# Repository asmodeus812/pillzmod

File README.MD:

# Pillz Mod for the Kinesis Advantage/Contoured

This project replaces my two previous forks ([kinesismod](https://github.com/dcpedit/kinesismod) and [kint](https://github.com/dcpedit/kint)) for adding Blackpill support to the Kinesis keyboard.  I've decided to merge all the features into a single PCB, add optional thumb cluster PCBs as part of the kit, and renamed the project to avoid confusion.  Below is a list of supported features.

* Supports Blackpill development board running QMK/Vial
* Supports Pill Bug wireless Bluetooth development board running ZMK
* Optional reversible thumb cluster PCB for left/right sides.  (Maintains original matrix wiring)
* 2u stabilizer support on thumb cluster

## "Pro" PCB Features

* Supports devlopment board with Pro-Micro footprint (Elite-C, Elite-Pi, Nice!Nano)
* Header for connecting up to 3 foot-pedals
* Piezo audio buzzer
* Header for extra data pin (Elite-C only)

## Split PCB (physically split Advantage 2)

_Seen from underneath (component side): right half on the left._

Two narrow boards in [`pcb-split/`](pcb-split/README.md), one per half, for
cutting the case in the middle. Each half has its own Nice!Nano, battery
socket, power switch and reset button, and connects to the same Molex and
Pillz thumb connectors at their original positions. Gerbers are in
`pcb-split/production`.

## Attribution

Credit goes to the following people for doing all the initial development on replacment PCBs for the Kinesis:
 * Aaron Silman's [kinesismod project](https://gitlab.com/Silman/kinesismod.git) ([blog](https://silman.io/project/kinesis_mod/))
 * Michael Stapelberg's [KinT project](https://github.com/kinx-project/kint) ([blog](https://michael.stapelberg.ch/posts/2020-07-09-kint-kinesis-keyboard-controller/))
 * Dmitry Nosachev's [Kin80 project](https://github.com/DmNosachev/kin80)

## Ordering PCBs from JLCPCB

The files needed for https://jlcpcb.com are located in the production folders:
* Choose `pcb-pro/production`, `pcb/production` or `pcb-split/production/left` + `right`
* `thumb-pcb/production`

Once uploaded, you place the order with the selected default options.  You can optionally change the solder mask color, which changes the final color of your PCB.

## Main PCB build guide
### Components
| Position | Description | Qty | Notes |
| -------- | ----------- | --- | ----- |
| J1-J4    | Molex 39-53-2135 | 2 - 6  | [Link](https://octopart.com/39-53-2135-molex-7670149?r=sp)
| J3-J4    | Molex 39-53-2134 | 0 - 2  | Contoured only, [Link](https://octopart.com/search?q=Molex+39-53-2134)
| U1       | Header pins (1x20) | 2 | Should come with dev board
| U1       | Headers (1x20) | 2 | To socket your dev board
| D1-D4    | 1.8mm LED | 4 | [Amazon](https://a.co/d/90uynIs)
| R1-R4    | 10k resistor | 4 | Affects LED brightness. Smaller = brighter |
|          | USB-C panel mount | 1 | [AliExpress](https://www.aliexpress.us/item/3256806463941289.html?spm=a2g0o.order_list.order_list_main.43.18a31802pDYB6d&gatewayAdapt=glo2usa), [Amazon](https://a.co/d/cRoqHqx)

### Blackpill Components
| Position | Description | Qty | Notes |
| -------- | ----------- | --- | ----- |
| U1       | Blackpill (STM32F411) | 1 | [WeAct Store](https://www.aliexpress.com/store/1101545918?spm=a2g0o.order_list.order_list_main.2.18a31802pDYB6d)

#### -or- Pill Bug for wireless build

| Description | Qty | Notes |
| ----------- | --- | ----- |
| Pill Bug | 1 | [MechWild Store](https://mechwild.com/product/pillbug/)
| 3.7V battery | 1 | [2000mAh](https://a.co/d/dVUdHxi)
| Power button | 1 | Optional, [10mm](https://a.co/d/i33uBM0) or [19mm](https://a.co/d/fYN6ZX5)

### Additional "Pro" Components

| Position | Description | Qty | Notes |
| -------- | ----------- | --- | ----- |
| U1       | Elite-C/Elite-Pi | 1 |
|          | 3.7V battery | 1 | [2000mAh](https://a.co/d/dVUdHxi)
| U2       | 74HC595      | 1 | [Amazon](https://a.co/d/eLX9kOY)
| U2       | 16-pin IC socket | 1 | [Amazon](https://a.co/d/5EaFAHo)
| D6-D8    | 1n4148 Diode | 3 | [Link](https://www.mouser.com/ProductDetail/512-1N4148TR)
| BZ1      | Piezo Buzzer | 1 | [Link](https://www.digikey.com/en/products/detail/tdk-corporation/PS1240P02BT/935924)
| SW1      | Reset button | 1 | [Link](https://www2.mouser.com/ProductDetail/Alps-Alpine/SKQGAEE010?qs=N5Jky1br14PyTRvcw7F3eQ%3D%3D)
| R5-R19   | 10k Resistor | 15| AVR/Elite-C Only [Link](https://www.mouser.com/ProductDetail/YAGEO/MFR-12FTF52-10K?qs=oAGoVhmvjhzLlUYKKBtdYQ%3D%3D), [Link](https://mou.sr/3xgqcNf)

#### -or- Nice!Nano for wireless build

| Description | Qty | Notes |
| ----------- | --- | ----- |
| Nice!Nano    | 1 | [Website](https://nicekeyboards.com/nice-nano/)
| 3.7V battery | 1 | [2000mAh](https://a.co/d/dVUdHxi)
| Power button | 1 | Optional, [10mm](https://a.co/d/i33uBM0) or [19mm](https://a.co/d/fYN6ZX5)

### Instructions

_NOTE: If you're using a battery that's larger than 500mAh, then bridge the charge boost jumper labeled JP1 with some solder.  This will increases the max charge rate from 100mA to 500mA. Doing this for small batteries (<500mAh) may cause explosions._

All components go on the side with the silkscreen labels (rectangles) EXCEPT for the LEDs.  First solder the header pins onto your development board, and the header sockets onto the PCB.  I prefer to use Mill-Max 310 series sockets because the pins are thin.  Then solder in the LED resistors, but NOT the actual LEDs yet.  The resistors can be SMD or through hole.

For a wireless build, you can now solder the battery wires/connector to the board.  Make sure the positive wire goes into "BAT+", and the negative wire goes into "BAT-".  If you're using a power button, make sure to wire it inline along the BAT+ wire so that it essentially opens and closes the circuit.

Insert your development board into the sockets on the PCB.

For the Molex connectors, I find that it's more convient to desolder the ones on the original PCB so that I don't have to purchase new ones.  Solder the connectors onto the PCB.

Flip the PCB over and insert the LEDs on the side of the PCB with no other components.  Make sure the short leg goes into the square pad, and bend the legs so that they stay in place.  Screw the PCB back into the keyboard case, making sure the LEDs are lined up with the existing case holes.  You can also adjust the height of the LED to move them closer to the status window if you'd like.  Once you're satisfied with the position of the LEDs, you can then solder them in place while the PCB is still mounted.

Lastly, plug the USB-C panel mount cable to into the development board, and secure the other end to the hole in the case.

### "Pro" Additional Instructions

The components required for this build and their position will depend on the development board you're using.  For example, pull-down resistors R5-R19 are only needed for AVR chips (Pro-Micro, Elite-C) since they don't support internal pull-downs for the row inputs.  Use the image below as a guide.

The Elite-C has an extra B0 pin that is broken out into the J10 pins.  You can use this to drive other components if you choose (ie. RGB strip, Solenoid)

* Pin 1 (square pad) - VCC
* Pin 2 - B0
* Pin 3 - GND

The J9 pins are for foot pedals and have the following assignment:

* Pin 1 (square pad) - Col6
* Pin 2 - Row0
* Pin 3 - Row1
* Pin 4 - Row2

Diodes D6-D8 are connected to the rows, so no additional diodes are needed in the pedals/switches.

### "Pro" Nice!Nano Additional Instructions

Mill-Max 310 sockets are recommended for socketing the Nice!Nano because thin pins are required for connecting the extra 3 pins in the middle.

The Nice!Nano is one pin short of supporting all 4 status lights on the Advantage.  If you want to utilize the unused numpad status LED as a power indicator, go ahead and short JP1 with some solder.

## Thumb cluster PCB build guide

The wiring for the thumb cluster (a.k.a. matrix wiring) has not been altered from original, so theoretically, they can be used in conjunction with any Kinesis PCB, including the stock one.

The PCB is also reversible, so you don't have to place separate orders for a "left" version and a "right" version.

### Components

| Description | Qty | Notes |
| ----------- | --- | ----- |
| 1N4148 SOD-123 diode | 12 | [Amazon](https://a.co/d/gsv8bGT)
| MX switch | 12 | Can desolder and reuse
| 2u screw-in stabilizer | 4 | [Link](https://divinikey.com/products/durock-v2-stabilizers-screw-in)
| Cable connector (1x10) | 4 | 2.54mm pitch (eg KF2510)
| Ribbon cable | 2 | >= 50mm length

### Instructions

You will need two PCBs for the thumb cluster, but since they're reversible, you will need to read the silkscreen to see if it's the left or right cluster.

First step is to solder all the 1N4148 diodes.  Orientation matters, so make sure the line on the diode faces same direction as the thicker white line on the PCB.  Place a dab of solder on ONE of the two diode pads.  Drop the diode into position (double checking the orientation), hold the diode in place with tweezers, and melt the solder you just added to the pad so that diode is held in place.  Now add solder to the opposite pad, thus holding the other diode leg in place.  Repeat for all the other diodes.

The connector for the ribbon cable can now be soldered onto the PCB, and will be on the same side as the diodes.  The pin pitch is 2.54mm, so any compatible connector/cable will work here.

Install the 2u stabilizers onto the PCB.

Now solder in your MX switches.  If you're reusing the original switches, desolder them from the original PCB, and remove the diode from inside the switch housing.  Using a switch opener will make this task much easier.

Mount the thumb clusters onto the keyboard and connect the ribbon cables.

## QMK firmware for "Pro"

* `firmware/pro_qmk_avr_default.bin`
* `firmware/pro_qmk_rp2040_default.uf2`

QMK source: https://github.com/dcpedit/qmk_firmware/tree/pillzmod/keyboards/dcpedit/pillzmod

## Vial firmware for Blackpill

* `firmware/blackpill_vial.bin`
* `firmware/dcpedit_kint_bp_vial_6layers.bin`

Source: https://github.com/dcpedit/vial-qmk/tree/pillzmod/keyboards/dcpedit/pillzmod

Remap keys: https://vial.rocks/

### Flashing firmware under Linux
The file firmware/dcpedit_kint_bp_vial_6layers.bin (or other) can simply be flashed to the Blackpill using the dfu-util. The dfu-util tool requires root privileges if settings are not accessible by the user.

Connect Blackpill to your Linux PC via USB C cable and start unit in DFU mode by holding bootp button and pressing reset button. Wait a second and release the bootp button.

Check the DFU devices by running
```
dfu-util -l
```
The Blackpill device should be visible.

Write the firmware to the device with
```
dfu-util -d 0483:df11 -a 0 -s 0x08000000 -D [PATH TO kint]/firmware/dcpedit_kint_bp_vial_6layers.bin
```

## Vial firmware for "Pro"

* `firmware/pro_vial_avr.hex`

Source: https://github.com/dcpedit/vial-qmk/tree/pillzmod/keyboards/dcpedit/pillzmod
(You will need to clone the entire branch since I had to make a core code change in `spi_master.c`)

## ZMK firmware for Pill Bug

* `firmware/zmk_default.uf2` - Default keymap
* `firmware/zmk_custom.uf2` - Support for up to 6 layers
* `firmware/zmk_reset.uf2` - Resets PillBug board for BT connectivity issue on MacOS      
* `firmware/zmk_studio.uf2` - Studio compatible (Progrm + Esc to unlock)

Source: https://github.com/dcpedit/zmk/tree/pillzmod/app/boards/shields/pillzmod

### Bluetooth with ZMK

The ZMK firmware has mappings for performing system tasks. By default there are 4 Bluetooth pairings saved to the keyboard but they do not switch automatically when adding new devices. So after you add the first device, you need to tell they keyboard to use Bluetooth slot 2 and so forth.
The keys to switch between are accessed by a different keyboard layer. This layer is opened by holding down the "Program" key at the very top right of the Kinesis and, while holding it, then clicking another key as follows:

* **Clear all saved Bluetooth profiles:** Program + F9
* **Bluetooth profile 1:** Program + F1
* **Bluetooth profile 2:** Program + F2
* **Bluetooth profile 3:** Program + F3
* **Bluetooth profile 4:** Program + F4
* **Enter bootloader mode (to upload UF2 files):** Program + - (the dash key just below program)

If you want to do a ZMK firmware build using GitHub actions, take a look at the following repository from keepitsimplejim:

https://github.com/keepitsimplejim/zmk-config-pillzmod-kinesis-adv

## ZMK firmware for "Pro" Nice!Nano

* `firmware/pro_zmk.uf2` - Default keymap
* `firmware/pro_zmk_studio.uf2` - Studio compatible (Progrm + Esc to unlock)

Source: https://github.com/dcpedit/zmk/tree/pillzmod/app/boards/shields/pillzmod_pro
Studio: https://zmk.studio/

## KiCad

All the PCBs were designed using KiCad, which is free and can be downloaded here: https://www.kicad.org/

For the thumb cluster PCB, I wasn't able to figure out how to have the left and right wiring co-exist without errors while sharing the same connector footprint.  My workaround was to first change the connector's reference designator to "J1", update the PCB from schematic, and wire up the left side.  Then I changed the reference designator to "J2", updated the PCB from schematic again, and wired up the right side.

If there are any KiCad experts out there that know of a more elegant solution, please let me know.

The production JLCPCB files are all generated with Fabrication Toolkit: https://github.com/bennymeg/Fabrication-Toolkit

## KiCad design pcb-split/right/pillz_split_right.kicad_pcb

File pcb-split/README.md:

# Pillz split boards (Kinesis Advantage 2)

Two narrow boards, one per half, replacing the single pillzmod "pro" board so
the case can be cut in the middle. Each half has its own nice!nano, battery,
power switch and reset button, and talks to the other half over BLE (ZMK split).

Derived from this repo's `pcb-pro` board ([dcpedit/pillzmod](https://github.com/dcpedit/pillzmod))
(CC BY 4.0). The connector footprints and their exact positions are copied from
that board, so the key-well flex cables and the Pillz thumb ribbons reach them
unchanged.

The component side (B) faces down into the case, the bare F side faces the
keys, as with the original board (its status LEDs were the only F-side parts).
The renders look at the component side, i.e. from underneath, so the right
half is on the left of the picture and the Molex connectors sit on the outer
edges, next to the key wells.

The Molex connectors and the nice!nano (on 8.5 mm sockets) use approximate
box models from `models.py`; the rest are stock KiCad models.

## Layout

| | Left (x 100–132.5) | Right (x 167.5–200) |
|---|---|---|
| Function row | J2, Molex 39-53-2135 | J1, Molex 39-53-2135 |
| Key well | J4, 39-53-2134 right angle (dual footprint, 2135 also fits) | J3, same |
| Thumb (Pillz thumb PCB ribbon) | J6, 1x10 2.54 mm | J5, 1x10 2.54 mm |
| Controller | U1 nice!nano, top level with the middle of J2, USB towards the top edge | U1, same against J1 |
| Reset / power | SW1 SKQG / SW2 C&K PCM12SMTR (slider facing down, inner edge kept clear) | same |
| Battery | J7 JST-PH 2.0 vertical, pin 1 = + | same |
| Mounting | one M3 hole between J2 and J4 | one M3 hole between J1 and J3 |

Boards are 32.5 x 86 mm, with the same top/bottom/outer edges as the original
board. All parts go on the B side (silkscreen side, facing down in the case),
as on the upstream board. `placement.png` and `routed.png` are seen from above.
The nice!nano is mounted components up (facing away from the PCB).

**Check the battery polarity before plugging it in.** JST-PH cells don't follow
a single standard; the silkscreen marks `+` / `-`.

## Matrix to controller

No shift register: 9 rows + 7 columns = 16 GPIO per half, wired directly.
Diodes are in the switches / thumb PCB, col2row as before.

| `&pro_micro` | Left | Right |
|---|---|---|
| 1 | ROW_0 | ROW_13 |
| 0 | ROW_1 | ROW_14 |
| 2 | COL_3 | ROW_12 |
| 3 | COL_4 | COL_5 |
| 4 | ROW_2 | COL_3 |
| 5 | ROW_3 | COL_4 |
| 6 | ROW_4 | ROW_10 |
| 7 | ROW_5 | ROW_9 |
| 8 | COL_5 | ROW_11 |
| 9 | COL_6 | COL_0 |
| 14 | COL_1 | COL_6 |
| 15 | COL_2 | ROW_8 |
| 18 | ROW_14 | ROW_7 |
| 19 | ROW_13 | ROW_6 |
| 20 | ROW_12 | COL_2 |
| 21 | COL_0 | COL_1 |
| 10, 16 | free | free |

Net names follow the original matrix (`RC(row, col)` in the old transform), so
the right half's rows are ROW_6..11 and ROW_12..14.

## Building / fab files

`routed.png`: left B.Cu, left F.Cu, right B.Cu, right F.Cu. GND is poured on
both layers. JLCPCB uploads are `production/pillz_split_left.zip` and
`production/pillz_split_right.zip` (2 layers, 1.6 mm, default options).

```sh
FREEROUTING_JAR=/path/to/freerouting-1.9.0.jar ./build.sh
```

`build.sh` regenerates both boards (`gen.py`), autoroutes them with
Freerouting, pours GND (`route.py`), fails on any DRC error or unrouted
connection, then exports Gerbers + drill files and zips them. Freerouting
1.9.0 opens its window while routing, so run it from a desktop session.

`gen.py` puts a 0.6 mm track/via keepout inside the outline because
Freerouting doesn't receive KiCad's copper-to-edge rule.

Freerouting isn't deterministic and occasionally leaves one net unrouted, so
`build.sh` re-routes a half (up to `TRIES=5`) until DRC is clean. The right
half has one locked pre-route (ROW_13, J1 pin 1 to pin 11 along the outer side
of J1) that the router could never find on its own.

## Regenerating placement only

KiCad 10 Python (the flatpak works):

```sh
F="flatpak run --filesystem=$PWD --command=python3 org.kicad.KiCad"
$F extract_upstream.py  # only to refresh lib/ from ../pcb-pro
$F gen.py
python3 models.py       # only when changing the approximate 3D models
```

`gen.py` stops with an error if a connector pad doesn't land exactly where it
was on the upstream board.

Parts and replacement cables with EU vendor links: [parts-links.md](parts-links.md).

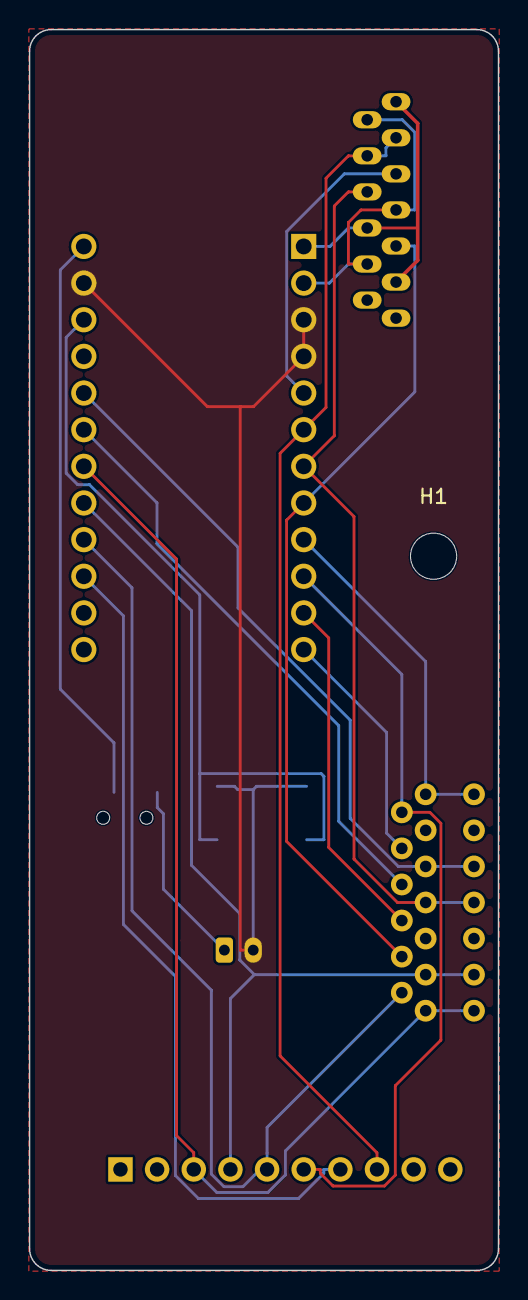
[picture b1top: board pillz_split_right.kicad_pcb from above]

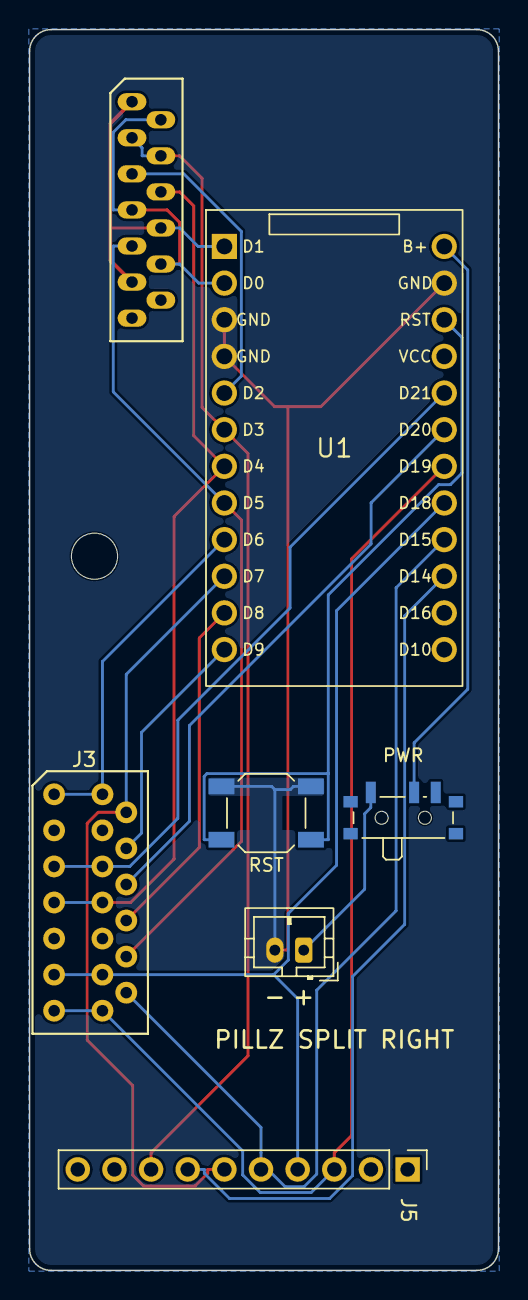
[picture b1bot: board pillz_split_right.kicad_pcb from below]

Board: 2 copper layers, 32.5 x 86.0 mm, 8 parts (7 on the bottom side), 20 nets.

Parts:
H1: MountingHole_3.2mm_M3
J1: Conn_01x13; Molex_0039532135
J3: Conn_01x13; Molex_039532134
J5: Conn_01x10; PinHeader_1x10_PillzThumb
J7: JST_PH_B2B-PH-K_1x02_P2.00mm_Vertical
SW1: SW_SPST_SKQG_WithoutStem
SW2: SW_SPDT_PCM12
U1: nice!nano v2; nice_nano_v2

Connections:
B+: SW2.2, U1.24
BAT+: J7.1, SW2.1
COL_0: J3.4, U1.12
COL_1: J3.5, U1.20
COL_2: J3.6, U1.19
COL_3: J1.6, J3.7, U1.7
COL_4: J1.9, J3.10, U1.8
COL_5: J1.3, J1.4, J5.8, U1.6
COL_6: J5.7, U1.15
GND: J7.2, SW1.2, U1.3, U1.4, U1.23
ROW_6: J3.13, J5.3, U1.18
ROW_7: J3.11, J5.4, U1.17
ROW_8: J3.12, J5.5, U1.16
ROW_9: J3.2, J5.6, U1.10
ROW_10: J3.1, U1.9
ROW_11: J3.8, U1.11
ROW_12: J1.5, U1.5
ROW_13: J1.1, J1.8, J1.11, U1.1
ROW_14: J1.2, J1.7, J1.10, U1.2
RST: SW1.1, U1.22

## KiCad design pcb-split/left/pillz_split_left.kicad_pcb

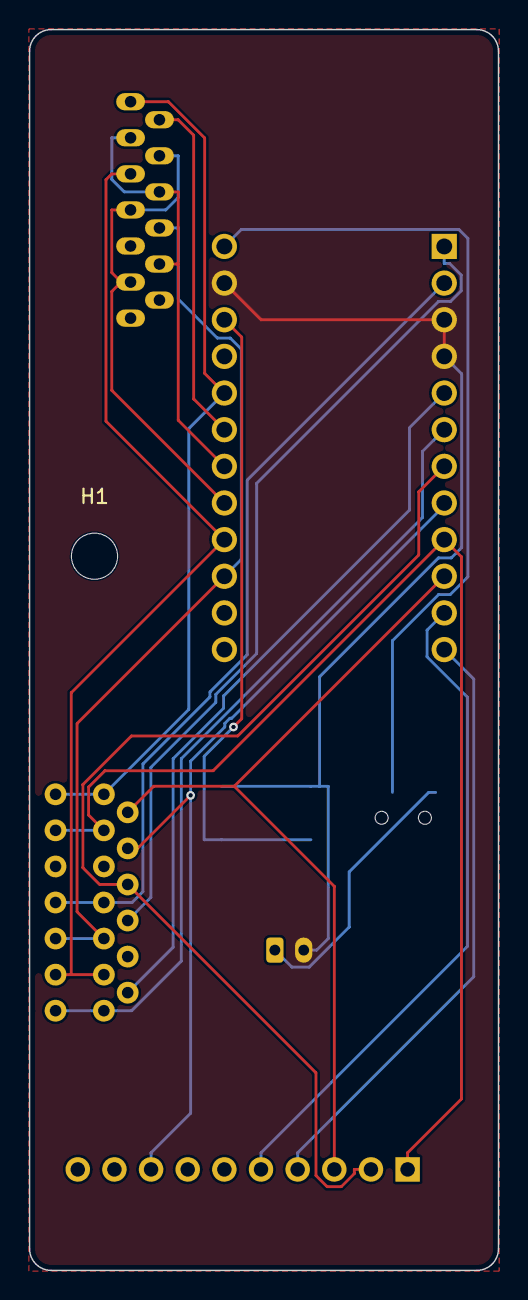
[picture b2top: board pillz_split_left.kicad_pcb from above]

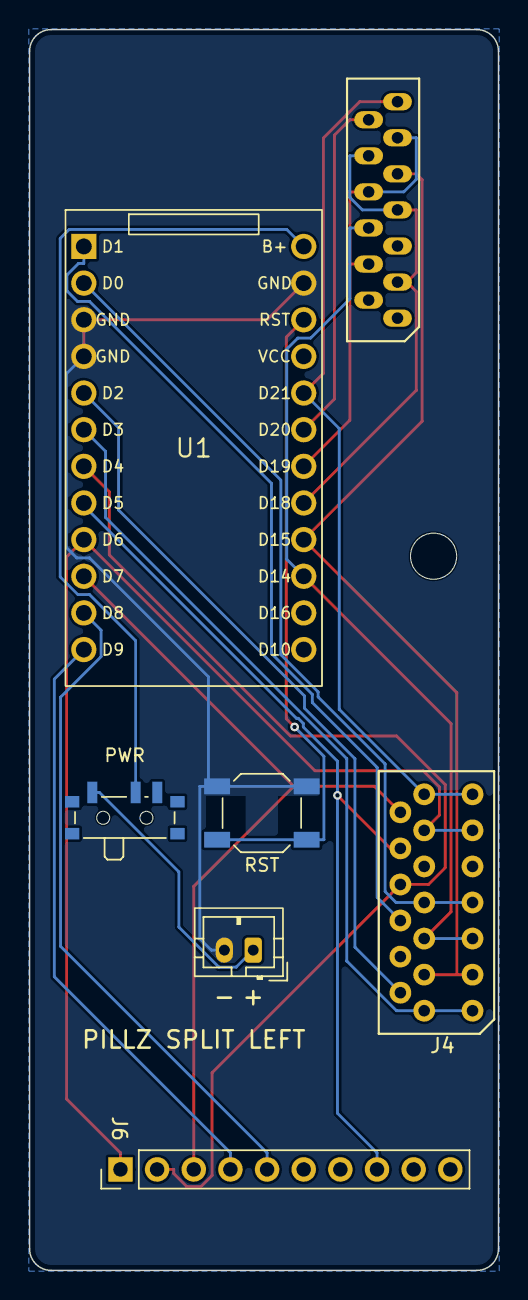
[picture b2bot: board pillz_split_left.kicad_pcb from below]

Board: 2 copper layers, 32.5 x 86.0 mm, 8 parts (7 on the bottom side), 20 nets.

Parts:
H1: MountingHole_3.2mm_M3
J2: Conn_01x13; Molex_0039532135
J4: Conn_01x13; Molex_039532134
J6: Conn_01x10; PinHeader_1x10_PillzThumb
J7: JST_PH_B2B-PH-K_1x02_P2.00mm_Vertical
SW1: SW_SPST_SKQG_WithoutStem
SW2: SW_SPDT_PCM12
U1: nice!nano v2; nice_nano_v2

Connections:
B+: SW2.2, U1.24
BAT+: J7.1, SW2.1
COL_0: J2.13, J4.13, U1.20
COL_1: J2.6, J4.5, U1.15
COL_2: J2.9, J4.3, U1.16
COL_3: J4.2, U1.5
COL_4: J4.1, U1.6
COL_5: J6.5, U1.11
COL_6: J6.4, U1.12
GND: J7.2, SW1.2, U1.3, U1.4, U1.23
ROW_0: J4.6, U1.1
ROW_1: J4.7, U1.2
ROW_2: J4.8, J6.2, U1.7
ROW_3: J4.10, J6.8, U1.8
ROW_4: J4.11, J6.1, U1.9
ROW_5: J4.12, J6.3, U1.10
ROW_12: J2.12, U1.19
ROW_13: J2.4, J2.8, J2.11, U1.18
ROW_14: J2.3, J2.7, J2.10, U1.17
RST: SW1.1, U1.22
